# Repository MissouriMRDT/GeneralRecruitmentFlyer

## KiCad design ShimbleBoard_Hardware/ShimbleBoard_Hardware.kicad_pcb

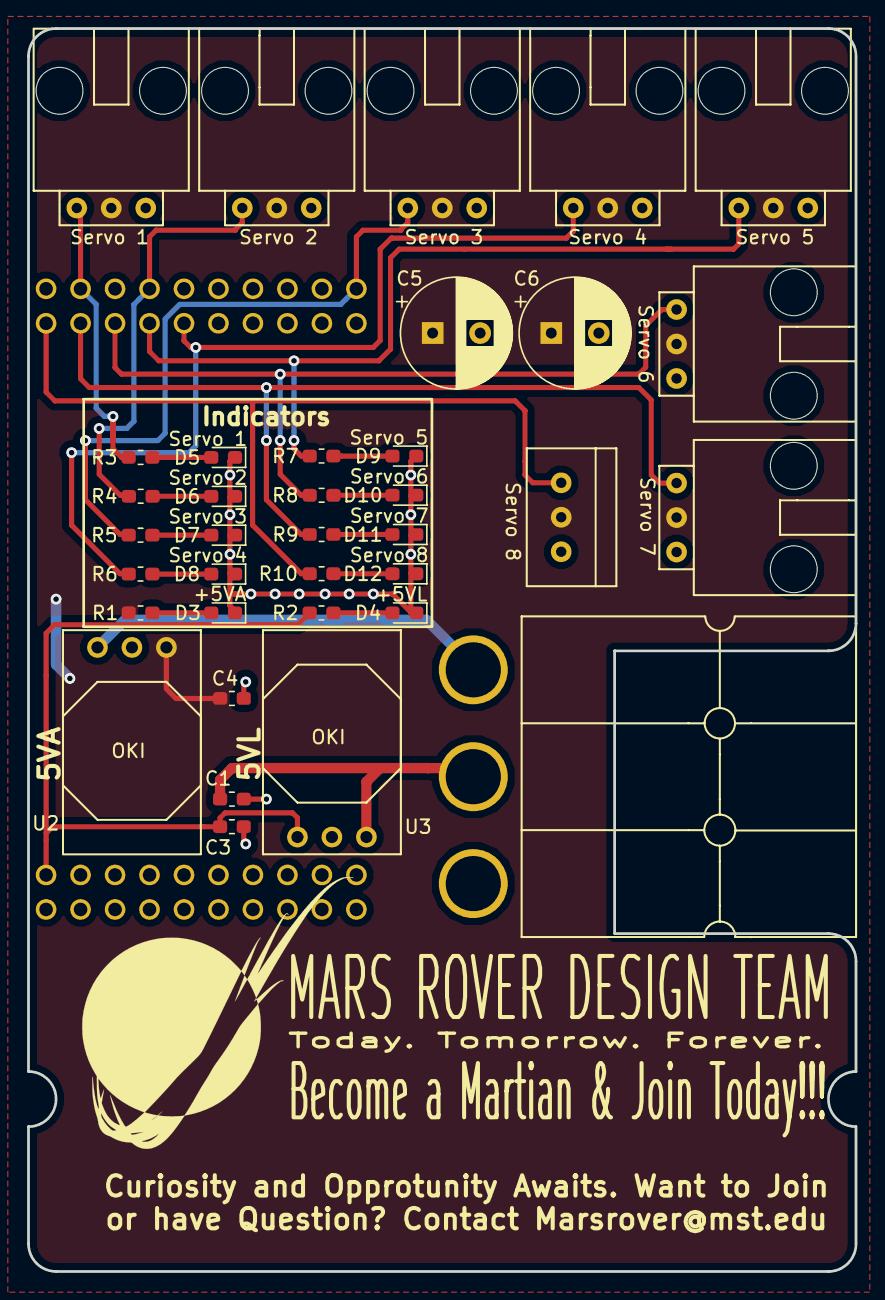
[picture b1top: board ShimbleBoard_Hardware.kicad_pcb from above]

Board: 2 copper layers, 61.0 x 91.6 mm, 38 parts (1 on the bottom side), 23 nets.

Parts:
C1, C2, C3, C4: 10uF; C_0603_1608Metric_Pad1.05x0.95mm_HandSolder
C5, C6: 470u; CP_Radial_D8.0mm_P3.50mm
Conn1: AndersonPP; Anderson_3_Horizontal_Side_by_Side
Conn2, Conn3, Conn4, Conn5, Conn6, Conn7, Conn8: Molex_SL_03; MOLEX_SL_03_Horizontal
Conn9: Molex_SL_03; MOLEX_SL_03_Vertical
D3: 5V_Act_LED; D_0603_1608Metric_Pad1.05x0.95mm_HandSolder
D4: 5V_Log_LED; D_0603_1608Metric_Pad1.05x0.95mm_HandSolder
D5: Ctrl_1_LED; D_0603_1608Metric_Pad1.05x0.95mm_HandSolder
D6: Ctrl_2_LED; D_0603_1608Metric_Pad1.05x0.95mm_HandSolder
D7: Ctrl_3_LED; D_0603_1608Metric_Pad1.05x0.95mm_HandSolder
D8: Ctrl_4_LED; D_0603_1608Metric_Pad1.05x0.95mm_HandSolder
D9: Ctrl_5_LED; D_0603_1608Metric_Pad1.05x0.95mm_HandSolder
D10: Ctrl_6_LED; D_0603_1608Metric_Pad1.05x0.95mm_HandSolder
D11: Ctrl_7_LED; D_0603_1608Metric_Pad1.05x0.95mm_HandSolder
D12: Ctrl_8_LED; D_0603_1608Metric_Pad1.05x0.95mm_HandSolder
R1, R2, R3, R4, R5, R6, R7, R8, R9, R10: 500; R_0603_1608Metric_Pad1.05x0.95mm_HandSolder
U1: TM4C129E_Launchpad; TM4C129E_Launchpad_X7_THT_BOTTOM
U2, U3: OKI; OKI_Horizontal

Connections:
+5VA: C4.1, C5.1, C6.1, Conn2.2, Conn3.2, Conn4.2, Conn5.2, Conn6.2, Conn7.2, Conn8.2, Conn9.2, R1.1, U2.3
+5VL: C3.1, R2.1, U1.+5V', U3.3
+12L: C1.1, Conn1.2, U3.1
+12VA: C2.2, Conn1.3, U2.1
GND: C1.2, C2.1, C3.2, C4.2, C5.2, C6.2, Conn1.1, Conn2.3, Conn3.3, Conn4.3, Conn5.3, Conn6.3, Conn7.3, Conn8.3, Conn9.3, D3.1, D4.1, D5.1, D6.1, D7.1, D8.1, D9.1, D10.1, D11.1, D12.1, U1.GND, U2.2, U3.2
unnamed: D3.2, R1.2
unnamed: D4.2, R2.2
unnamed: D5.2, R3.2
unnamed: D6.2, R4.2
unnamed: D7.2, R5.2
unnamed: D8.2, R6.2
unnamed: D9.2, R7.2
unnamed: D10.2, R8.2
unnamed: D11.2, R9.2
unnamed: D12.2, R10.2
Servo_1_Ctrl: Conn2.1, R3.1, U1.PM7
Servo_2_Ctrl: Conn3.1, R4.1, U1.PA7
Servo_3_Ctrl: Conn4.1, R5.1, U1.PM6
Servo_4_Ctrl: Conn5.1, R6.1, U1.PM1
Servo_5_Ctrl: Conn6.1, R7.1, U1.PM0
Servo_6_Ctrl: Conn7.1, R8.1, U1.PK5
Servo_7_Ctrl: Conn8.1, R9.1, U1.PK4
Servo_8_Ctrl: Conn9.1, R10.1, U1.PG1

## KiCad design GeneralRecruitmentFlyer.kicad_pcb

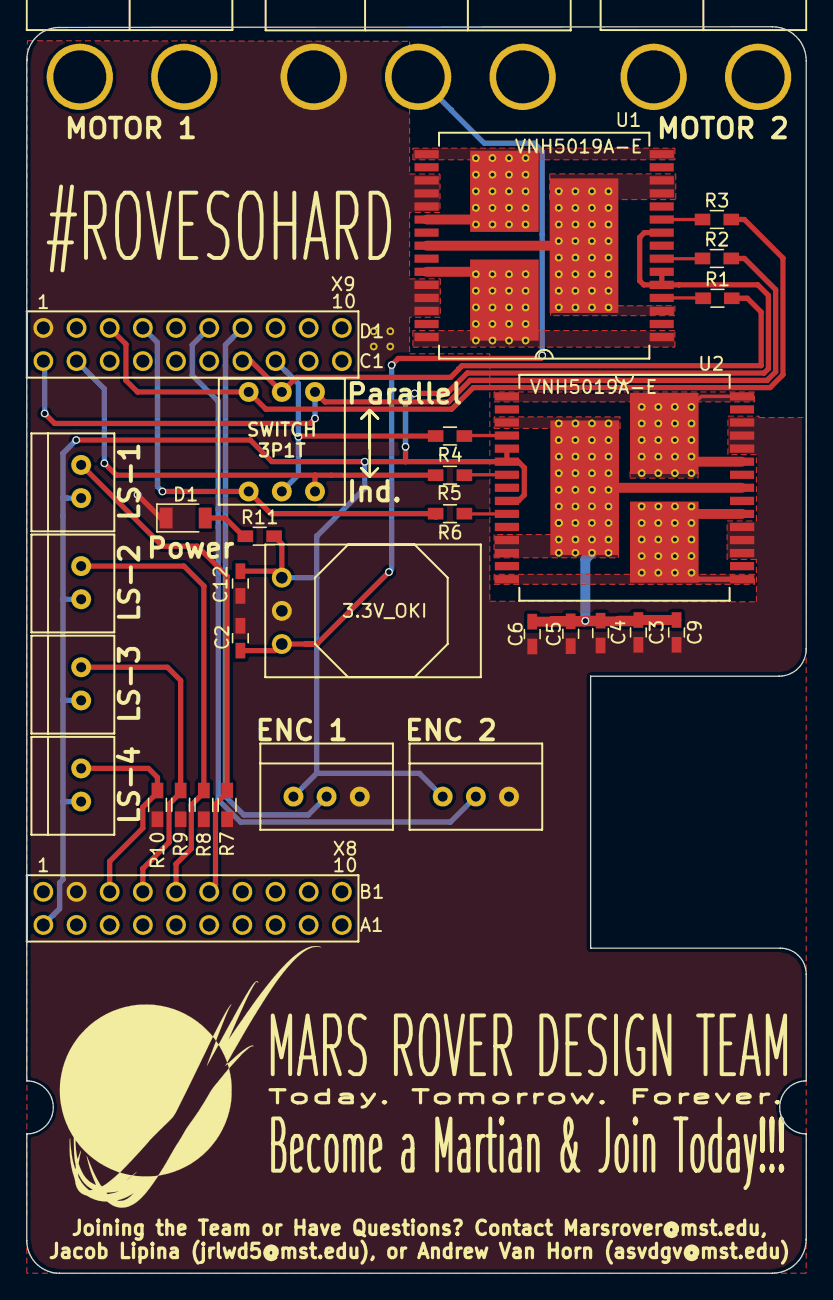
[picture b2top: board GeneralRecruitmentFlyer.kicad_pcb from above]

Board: 2 copper layers, 59.7 x 95.5 mm, 33 parts (0 on the bottom side), 27 nets.

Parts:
C1: Anderson_3; Anderson_3_Horisontal_Side_by_Side
C2, C3, C5, C6, C9, C12: 10u; C_0603_HandSoldering
C4: .1u; C_0603_HandSoldering
C7, C8: Anderson-2; Anderson_2_Horisontal_Side_by_Side
D1: LED; D_1206
R1, R2, R3, R4, R5, R6: 1K; R_0603_HandSoldering
R7, R8, R9, R10: 10K; R_0603_HandSoldering
R11: 330; R_0603_HandSoldering
SW1: 3P1T_Fused; 3P1T_Switch
U1, U2: VNH5019A-E; MultiPowerSO_30
U3: 3.3V_OKI; OKI_Horisontal
U4: LS_1; MOLEX_SL_2_Vertical
U5: LS_2; MOLEX_SL_2_Vertical
U6: TM4C129E_Launchpad_X9
U7, U8: Picoblade-3; MOLEX_SL_3_Vertical
U9: LS_3; MOLEX_SL_2_Vertical
U10: LS_4; MOLEX_SL_2_Vertical

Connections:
+3V3: C12.1, R11.2, U1.5, U1.6, U1.9, U2.5, U2.6, U2.9, U3.3, U4.1, U5.1, U6.+3V3, U7.1, U8.1, U9.1, U10.1
+12V: C1.1, C3.1, C4.1, C5.1, C6.1, C9.1, U1.3, U1.12, U1.13, U1.23, U1.32, U2.3, U2.12, U2.13, U2.23, U2.32
/12V_Logic: C1.2, C2.1, U3.1
/Out_A1: C7.1, U1.1, U1.25, U1.30, U1.31
/Out_A2: C8.1, U2.1, U2.25, U2.30, U2.31
/Out_B1: C7.2, U1.15, U1.16, U1.21, U1.33
/Out_B2: C8.2, U2.15, U2.16, U2.21, U2.33
Encoder1_PWM: U6.PD0, U7.2
Encoder2_PWM: U6.PD1, U8.2
GND: C1.3, C2.2, C3.2, C4.2, C5.2, C6.2, C9.2, C12.2, D1.1, R7.2, R8.2, R9.2, R10.2, U1.18, U1.19, U1.20, U1.26, U1.27, U1.28, U2.18, U2.19, U2.20, U2.26, U2.27, U2.28, U3.2, U6.GND, U7.3, U8.3
IN_A1: R1.2, SW1.3, U6.PL0
IN_A2: R4.2, SW1.4, U6.PL1
IN_B1: R3.2, SW1.1, U6.PH2
IN_B2: R6.2, SW1.2, U6.PH3
LS_1: R7.1, U4.2, U6.PE3
LS_2: R8.1, U5.2, U6.PE2
LS_3: R9.1, U6.PE1, U9.2
LS_4: R10.1, U6.PE0, U10.2
unnamed: D1.2, R11.1
unnamed: R1.1, U1.4
unnamed: R2.1, U1.7
unnamed: R3.1, U1.10
unnamed: R4.1, U2.4
unnamed: R5.1, U2.7
unnamed: R6.1, U2.10
PWM1: R2.2, SW1.5, U6.PF1
PWM2: R5.2, SW1.6, U6.PF2

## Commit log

2018-08-08 Drill Board Converted to a Handout Flyer
    General flyer to hand out to interested students.
2018-08-13 Added Gerbs
2018-08-22 Fixed Van's email
2019-07-27 Gimbal recruitment board
2019-08-02 nav board

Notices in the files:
parts and their libraries:
Copyright 2016 Accelerated Designs. All rights reserved.
